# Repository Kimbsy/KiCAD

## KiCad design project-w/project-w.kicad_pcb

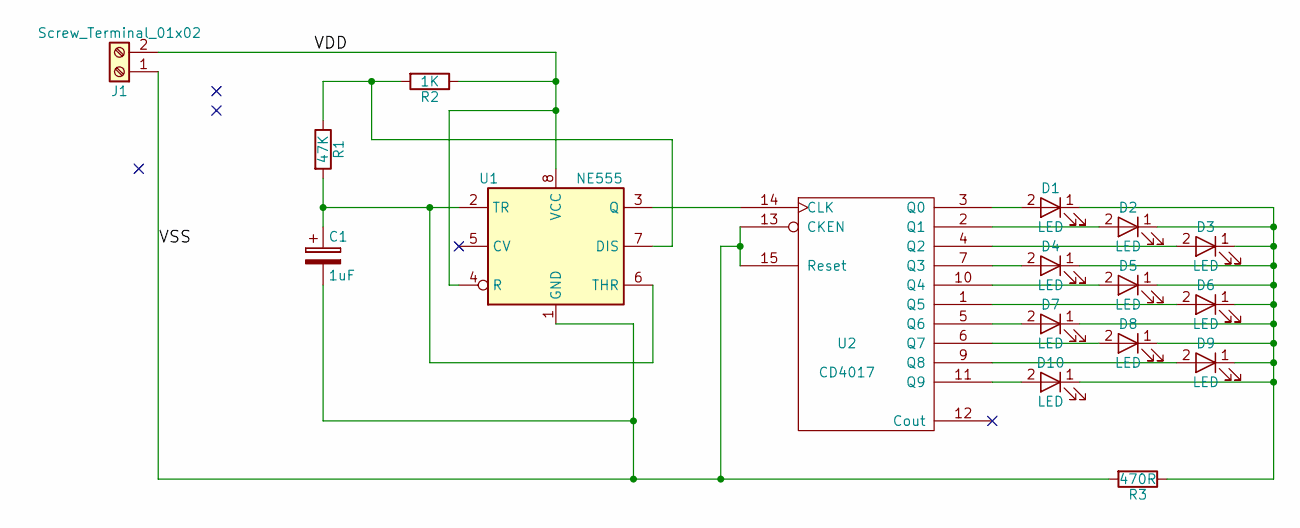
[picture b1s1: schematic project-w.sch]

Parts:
C1: 1uF; CP_Radial_D5.0mm_P2.00mm
D1, D2, D3, D4, D5, D6, D7, D8, D9, D10: LED; LED_D3.0mm
J1: Screw_Terminal_01x02; TerminalBlock_bornier-2_P5.08mm
R1: 47K; R_Axial_DIN0207_L6.3mm_D2.5mm_P7.62mm_Horizontal
R2: 1K; R_Axial_DIN0207_L6.3mm_D2.5mm_P7.62mm_Horizontal
R3: 470R; R_Axial_DIN0204_L3.6mm_D1.6mm_P5.08mm_Horizontal
U1: NE555; DIP-8_W7.62mm
U2: CD4017; DIP-16_W7.62mm

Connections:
unnamed: C1.1, R1.2, U1.2 (TR), U1.6 (THR)
unnamed: D1.1 (K), D2.1 (K), D3.1 (K), D4.1 (K), D5.1 (K), D6.1 (K), D7.1 (K), D8.1 (K), D9.1 (K), D10.1 (K), R3.1
unnamed: D1.2 (A), U2.3 (Q0)
unnamed: D2.2 (A), U2.2 (Q1)
unnamed: D3.2 (A), U2.4 (Q2)
unnamed: D4.2 (A), U2.7 (Q3)
unnamed: D5.2 (A), U2.10 (Q4)
unnamed: D6.2 (A), U2.1 (Q5)
unnamed: D7.2 (A), U2.5 (Q6)
unnamed: D8.2 (A), U2.6 (Q7)
unnamed: D9.2 (A), U2.9 (Q8)
unnamed: D10.2 (A), U2.11 (Q9)
unnamed: R1.1, R2.2, U1.7 (DIS)
unnamed: U1.3 (Q), U2.14 (CLK)
VDD: J1.2, R2.1, U1.4 (R), U1.8 (VCC), U2.16 (VDD)
VSS: C1.2, J1.1, R3.2, U1.1 (GND), U2.8 (VSS), U2.13 (CKEN), U2.15 (Reset)

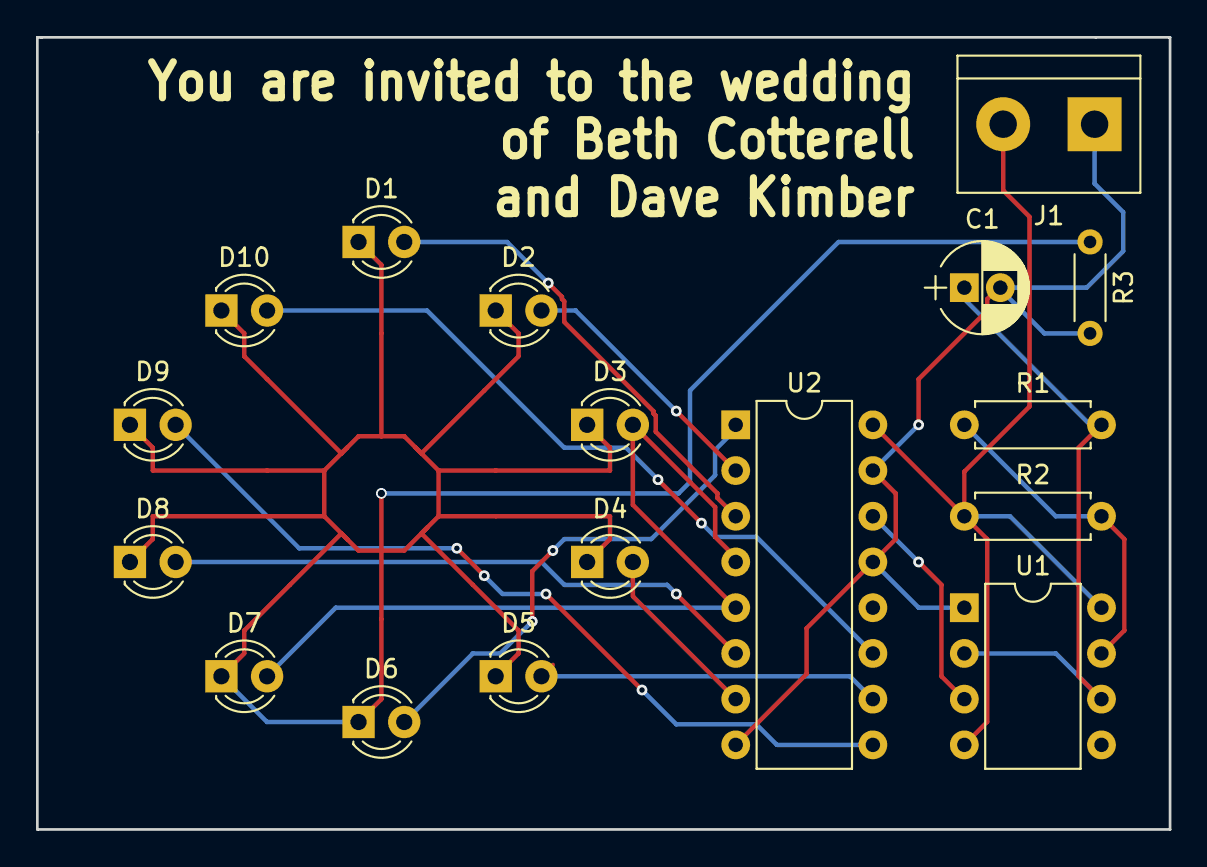
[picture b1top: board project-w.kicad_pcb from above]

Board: 2 copper layers, 62.9 x 44.0 mm, 17 parts (0 on the bottom side), 16 nets.

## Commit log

2018-01-22 initial commit, schematic, netlist, footprints etc done
2018-01-23 adding trace routes
2018-01-23 adding more space for silk screening
2018-01-23 adding example text
2018-01-23 trying to fix 3d models
2018-01-27 updating schematic to fix VSS VDD issues
2018-04-11 generated files for naked prototype
2018-05-16 updating schematic, fixing ordering issues, changin power connection
2018-06-13 fixes for prototype version 3
